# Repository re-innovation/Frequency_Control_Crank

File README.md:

# Frequency_Control_Crank

A crank handled swicth that controls power to things when turned.
This was built for an update to the Kinetiscopes from Ben Wigley.
Some ifnormation and video is available here:

https://www.re-innovation.co.uk/portfolio/kinetiscopes-a-lost-paradise/

This repository has the arduino nano control code, the design files for the magnetic sensor and datasheets for the control board used.
It also includes some photos.

To Do:

* Upload photos
* Do dimensioned design for future use

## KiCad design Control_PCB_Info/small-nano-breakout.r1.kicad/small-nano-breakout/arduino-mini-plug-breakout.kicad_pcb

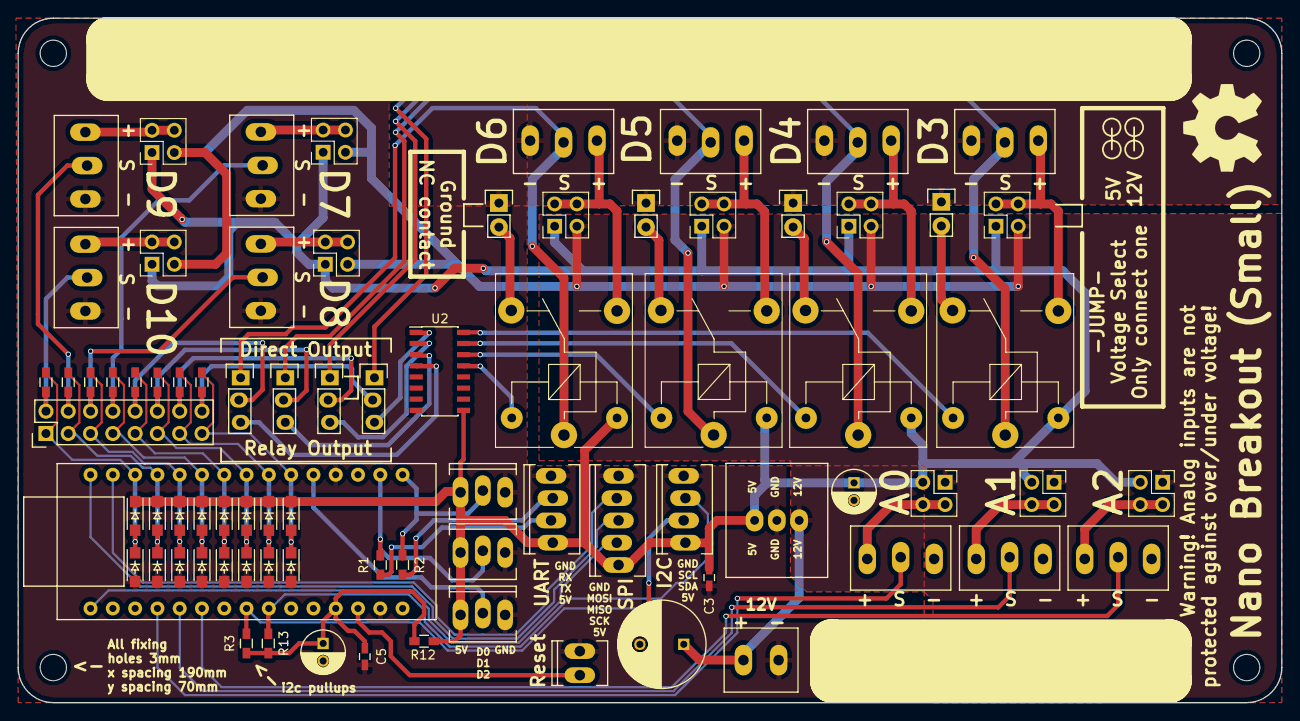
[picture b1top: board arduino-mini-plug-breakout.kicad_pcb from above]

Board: 2 copper layers, 144.0 x 78.0 mm, 85 parts (0 on the bottom side), 61 nets.

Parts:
BRD1: MOUNTING-HOLE-1; MountingHole_3mm
BRD2: MOUNTING-HOLE-2; MountingHole_3mm
BRD3: MOUNTING-HOLE-3; MountingHole_3mm
BRD4: MOUNTING-HOLE-4; MountingHole_3mm
BRD5: OSHW-LOGO; OSHW-logo_silkscreen-front_10mm
C1: 100u; C_Radial_D10_L13_P5
C2, C4: 10u; C_Radial_D5_L11_P2
C3, C5: 100n; C_0603_HandSoldering
COMM1: MOLEX; Socket_MOLEX-KK-RM2-54mm_Lock_5pin_straight
COMM2, COMM3: MOLEX; Socket_MOLEX-KK-RM2-54mm_Lock_4pin_straight
CONA0, CONA1, CONA2: PLUGGABLE; Standard_3Way_OffsetHoles
COND3, COND4, COND5, COND6, COND7, COND8, COND9, COND10: PLUGGABLE; Standard_3Way_OffsetHoles
D1, D2, D3, D4, D5, D6, D7, D8, D9, D10, D11, D12, D13, D14, D15, D16: ANY; SOD-123
IO0, IO1, IO2: MOLEX; Socket_MOLEX-KK-RM2-54mm_Lock_3pin_straight
JP1: GSEL3; Pin_Header_Straight_1x02
JP2: GSEL4; Pin_Header_Straight_1x02
JP3: GSEL5; Pin_Header_Straight_1x02
JP4: GSEL6; Pin_Header_Straight_1x02
JP9, JP10, JP11, JP12: RLY_SEL3; Pin_Header_Straight_1x03
P1: CONN_02X08; Pin_Header_Straight_2x08
PCON1: 12V; Standard_2Way_OffsetHoles
PSEL3, PSEL4, PSEL5, PSEL6, PSEL7, PSEL8, PSEL9, PSEL10: CONN_02X02; Pin_Header_Straight_2x02_Pitch2.54mm
PSELA0, PSELA1, PSELA2: CONN_02X02; Pin_Header_Straight_2x02_Pitch2.54mm
R1, R2: 1K; R_0603_HandSoldering
R3, R13: 4K7; R_0603_HandSoldering
R4, R5, R6, R7, R8, R9, R10, R11: 10K; R_0603_HandSoldering
R12: 1R; R_0603_HandSoldering
REG1: RECOM; DCDC-Conv_Recom_R-78HBxx-0.5
RLY1, RLY2, RLY3, RLY4: relay-spdt; Relay_SPDT_SANYOU_SRD_Series_Form_C
RST1: MOLEX; Socket_MOLEX-KK-RM2-54mm_Lock_2pin_straight
U1: arduino_nano; nano
U2: ULN2003; SOIC-16_3.9x9.9mm_Pitch1.27mm

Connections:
+5V: C2.1, C3.1, COMM1.1, COMM2.1, COMM3.1, D1.1, D3.1, D5.1, D7.1, D9.1, D11.1, D13.1, D15.1, IO0.1, IO1.1, IO2.1, PSEL3.1, PSEL4.1, PSEL5.1, PSEL6.1, PSEL7.1, PSEL8.1, PSEL9.1, PSEL10.1, PSELA0.3, PSELA1.3, PSELA2.3, R12.2, REG1.3, RLY1.2, RLY2.2, RLY3.2, RLY4.2, U2.9
+5VARD: C4.1, C5.1, R3.1, R12.1, R13.1, U1.12
+12V: C1.1, PCON1.1, PSEL3.3, PSEL4.3, PSEL5.3, PSEL6.3, PSEL7.3, PSEL8.3, PSEL9.3, PSEL10.3, PSELA0.1, PSELA1.1, PSELA2.1, REG1.1
/analog_io/A0: CONA0.2, U1.4
/analog_io/A1: CONA1.2, U1.5
/analog_io/A2: CONA2.2, U1.6
/analog_io/PSELA0: CONA0.1, PSELA0.2, PSELA0.4
/analog_io/PSELA1: CONA1.1, PSELA1.2, PSELA1.4
/analog_io/PSELA2: CONA2.1, PSELA2.2, PSELA2.4
/digital_io/D3-OUT: COND3.2, JP9.1, RLY1.1
/digital_io/D3-RLY: JP9.3, U2.1
/digital_io/D4-OUT: COND4.2, JP10.1, RLY2.1
/digital_io/D4-RLY: JP10.3, U2.2
/digital_io/D5-OUT: COND5.2, JP11.1, RLY3.1
/digital_io/D5-RLY: JP11.3, U2.3
/digital_io/D6-OUT: COND6.2, JP12.1, RLY4.1
/digital_io/D6-RLY: JP12.3, U2.4
/digital_io/D7-OUT: COND7.2, P1.8, R6.1
/digital_io/D8-OUT: COND8.2, P1.6, R10.1
/digital_io/D9-OUT: COND9.2, P1.4, R7.1
/digital_io/D10-OUT: COND10.2, P1.2, R11.1
/digital_io/GSEL3: JP1.2, RLY1.4
/digital_io/GSEL4: JP2.2, RLY2.4
/digital_io/GSEL5: JP3.2, RLY3.4
/digital_io/GSEL6: JP4.2, RLY4.4
/digital_io/PSEL3: COND3.1, PSEL3.2, PSEL3.4, RLY1.3
/digital_io/PSEL4: COND4.1, PSEL4.2, PSEL4.4, RLY2.3
/digital_io/PSEL5: COND5.1, PSEL5.2, PSEL5.4, RLY3.3
/digital_io/PSEL6: COND6.1, PSEL6.2, PSEL6.4, RLY4.3
/digital_io/PSEL7: COND7.1, PSEL7.2, PSEL7.4
/digital_io/PSEL8: COND8.1, PSEL8.2, PSEL8.4
/digital_io/PSEL9: COND9.1, PSEL9.2, PSEL9.4
/digital_io/PSEL10: COND10.1, PSEL10.2, PSEL10.4
/digital_io/RLY3: RLY1.5, U2.16
/digital_io/RLY4: RLY2.5, U2.15
/digital_io/RLY5: RLY3.5, U2.14
/digital_io/RLY6: RLY4.5, U2.13
/misc_io/D0: IO0.2, R2.2, U1.16
/misc_io/D1: IO1.2, R1.2, U1.17
/misc_io/D2: IO2.2, U1.20
/misc_io/RST: RST1.1, U1.13
/misc_io/RX: COMM3.3, R2.1
/misc_io/TX: COMM3.2, R1.1
/mode_selection/D3: D1.2, D2.1, P1.15, R4.2, U1.21
/mode_selection/D3-BYPASS: JP9.2, P1.16, R4.1
/mode_selection/D4: D3.2, D4.1, P1.13, R8.2, U1.22
/mode_selection/D4-BYPASS: JP10.2, P1.14, R8.1
/mode_selection/D5: D5.2, D6.1, P1.11, R5.2, U1.23
/mode_selection/D5-BYPASS: JP11.2, P1.12, R5.1
/mode_selection/D6: D7.2, D8.1, P1.9, R9.2, U1.24
/mode_selection/D6-BYPASS: JP12.2, P1.10, R9.1
/mode_selection/D7: D9.2, D10.1, P1.7, R6.2, U1.25
/mode_selection/D8: D11.2, D12.1, P1.5, R10.2, U1.26
/mode_selection/D9: D13.2, D14.1, P1.3, R7.2, U1.27
/mode_selection/D10: D15.2, D16.1, P1.1, R11.2, U1.28
/nano/A4/SDA: COMM2.2, R3.2, U1.8
/nano/A5/SCL: COMM2.3, R13.2, U1.9
/nano/D11/MOSI: COMM1.4, U1.29
/nano/D12/MISO: COMM1.3, U1.30
/nano/D13/SCK: COMM1.2, U1.1
GND: C1.2, C2.2, C3.2, C4.2, C5.2, COMM1.5, COMM2.4, COMM3.4, CONA0.3, CONA1.3, CONA2.3, COND3.3, COND4.3, COND5.3, COND6.3, COND7.3, COND8.3, COND9.3, COND10.3, D2.2, D4.2, D6.2, D8.2, D10.2, D12.2, D14.2, D16.2, IO0.3, IO1.3, IO2.3, JP1.1, JP2.1, JP3.1, JP4.1, PCON1.2, REG1.2, RST1.2, U1.14, U1.19, U2.8

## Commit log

2018-09-06 Added main code and datasheet info
